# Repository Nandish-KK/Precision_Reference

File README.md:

#  2.5V Precision Reference

A compact 2.5V precision voltage reference module, ideal for use as a standalone reference when building analog circuit prototypes or for verifying the accuracy of your multimeter’s voltage range over time.

## Prototyping and Testing
The design required a low voltage source to make the Reference module as compact as possible. A CR2032 coin cell at 3V is the ideal candidate.
This requirement turns into a design constraint as the minimum operating voltage stated in the datasheet for the REF03 is 4.5V. The REF03 is a Low-Dropout
type Reference and is the best option to design a voltage reference due to its extremly low Temperature coefficient (10-50 ppm/C) and requires minimum passive components to operate.

### Charge pump
In order to generate a voltage that is sufficient to drive the REF03 above the minimum operating voltage a charge pump topology is implemented.
The charge pump consists of a variable frequency oscillator and a voltage doubler circuit. The oscillator is constructed using an SN74 logic inverter with
hysteresis and an RC feedback network. At 3V input, the circuit can generate a maximum of 5.6V but drops drastically depending on the load.
The quiescent current of the REF03 is around 1 mA, which also gives a bit of headroom to even sink some current into the DUT. 

Oscillator: SN74LVC2G14DBV sot23-6 soldered with passives on a proto pcb.

### Testing

The following tests are performed with a wide bandwidth. You can see some high-frequency noise along with voltage ripples at the charge pump output (with REF03 connected). After further testing, it seems like the ripples are generated from the oscillator.
The SN74LVC2G14DBV has a fast rising edge of about 4ns; this, combined with Schmitt trigger action and the board's parasitics, results in a ringing behavior at the output. This high-frequency component seems to bypass even the REF03 and appears at the reference voltage. Implementation of an additional filtering circuit might be necessary. Another option is to find an inverter with a slower rise time.

Tested the reference output with coax to make sure the noise isn't from a background source. The other two channels are connected to the charge pump output and the oscillator output.

- Yellow : Reference Output
- Pink :   Charge pump Output
- Blue :   Oscillator  Output

#### No Load condition

The voltmeter isn't accurate and is used to observe voltage drops with and without load.

With a high-impedance load like a multimeter (essentially no load) attached to the output of the REF03, the voltage is quite stable and exhibits minimal ripple.
The output voltage is around 5.47V with a ripple of 36.25mV peak-to-peak (7.54mV RMS). The setup also draws around 6mA, which is quite high. Since the REF03 draws 1-2 mA, the additional current should be consumed by the oscillator. This is not a good circuit to leave ON for a long time; it will drain the CR2032 in a day or two. Make sure to turn off the module with the toggle switch after use to prevent it from going completely dead. 

#### 10mA Load 
The charge pump output voltage seems to drop significantly if the REF03 starts to sink current to the load. The REF03 is rated to sink up to 24mA, but this much current will render my simple charge pump setup useless. I did end up testing the current sink capability of the prototype using a variable potentiometer, and it seems like the voltage starts to drop around 16mA of total current draw. This indicates that the prototype PCB was able to sink 10mA from the REF03 (remember that the circuit draws 6mA at idle). The voltage dropping trend was observed using a 3.5-digit multimeter, and results may vary with more accurate meters.

While sinking 16mA of total current, the charge pump output drops to around 4.87 volts while also exhibiting some ripple characteristics. The ripple is around 300mV peak-to-peak with a frequency that corresponds to the charge pump switching frequency. Thankfully, the ripple doesn't reflect on the output of the REF03. Note that these ripples can be minimized with appropriate capacitance.

## Output Stability

Currently, I don't own a precision multimeter, which makes it harder to measure how stable the output voltage really is. What I do own is a DSO with a 12-bit ADC (SDS800X), and it seems to read the voltage accurately up to 4 digits easily. The high-frequency noise at the output seems a bit annoying and likely skews the results a bit.

Reference voltage with No filter(Coupling: DC , BW: 20MHz)

## Filtering
In the end, I attempted to filter out the high-frequency noise using a simple RC filter with a cutoff frequency of around 1.5 kHz to achieve a more stable result. I also substituted the resistor with a ferrite bead. Both methods worked well in attenuating the noise. Although the filter did not eliminate it entirely, the noise was attenuated by approximately 20 dB when using the ferrite bead.

Noise measurement with a Ferrite Bead Pi Filter (Coupling: AC , BW: 20MHz)

Reference voltage with Ferrite Bead and a 10uF capacitor filter(Coupling: DC , BW: 20MHz)

## PCB Layout
The following schematic and PCB are designed with KiCad 9.

## Renders
- Tools:
  - pcb2blender addon for KiCad
  - Blender

---
## Dimensions

- PCB Diameter: 45mm
- Binding Post Spacing: 19.05mm 
- Mounting Holes: 2.2mm

## PCB Features

- Single coin cell operation (CR2032).
- Trim pot for fine adjustment of output voltage.
- 4mm BNC terminal with 3/4" spacing.
- Adjustment range: 2.3V - 2.8V.
- Compact design with M2 mounting holes and toggle switch.

---

## Datasheet

Datasheet: [Precision 2.5V, 5.0V, and 10.0V Voltage References](https://www.analog.com/media/en/technical-documentation/data-sheets/ref01_02_03.pdf)

```plaintext

## Some Design Afterthought's

- The REF03 datasheet specifies a minimum operating voltage of 4.5 V.
- However, during testing, the output remained stable down to 3 V with no load.
- If your application sinks significant current, ensure the supply voltage remains well above the minimum — ideally with a low-voltage cutoff circuit.
- The current consumption is quite high for operating from a single cell. Needs further investigation of the charge pump circuit.
- Also, the toggle switch seems to be upside down... D'oh!

```

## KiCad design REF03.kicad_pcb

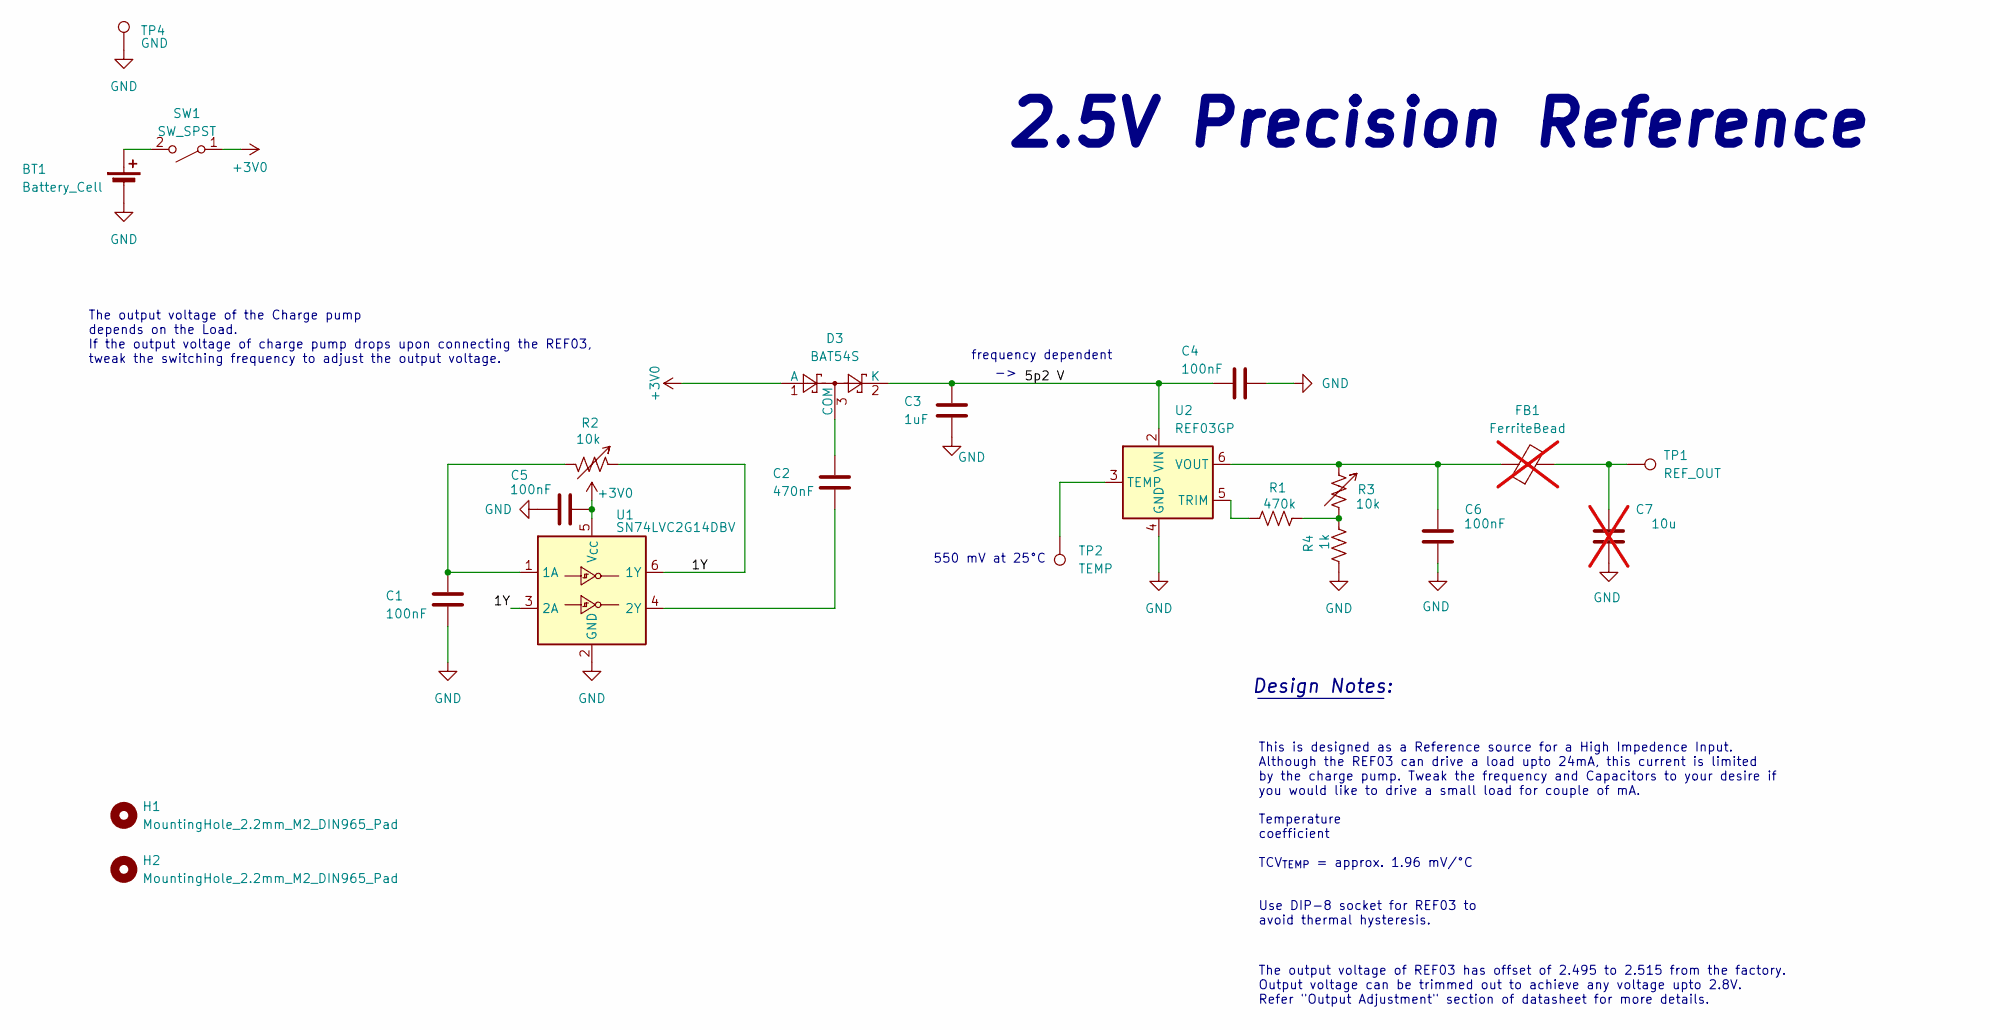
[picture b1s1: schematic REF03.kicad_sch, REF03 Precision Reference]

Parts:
BT1: Battery_Cell; BatteryHolder_Multicomp_BC-2001_1x2032
C1, C4, C5, C6: 100nF; C_0805_2012Metric
C2: 470nF; C_0805_2012Metric
C3: 1uF; C_1206_3216Metric
C7: 10u; C_0805_2012Metric; not fitted
D3: BAT54S; SOT-23
FB1: FerriteBead; L_0805_2012Metric; not fitted
H1, H2: MountingHole_2.2mm_M2_DIN965_Pad
R1: 470k; R_1206_3216Metric
R2, R3: 10k; Potentiometer_Bourns_3214G_Horizontal
R4: 1k; R_1206_3216Metric
SW1: SW_SPST; SW_Slide-03_Wuerth-WS-SLTV_10x2.5x6.4_P2.54mm
TP1: REF_OUT; TestPoint_Loop_D2.50mm_Drill1.0mm
TP2: TEMP; TestPoint_Pad_2.5x2.5mm
TP4: GND; TestPoint_Loop_D2.50mm_Drill1.0mm
U1: SN74LVC2G14DBV; SOT-23-6
U2: REF03GP; PowerIntegrations_SMD-8

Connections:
+3V0: C5.2, D3.1 (A), SW1.1 (A), U1.5 (V_{CC})
/1Y: R2.1, U1.3 (2A), U1.6 (1Y)
/5p2 V: C3.1, C4.2, D3.2 (K), U2.2 (VIN)
GND: BT1.2 (-), C1.2, C3.2, C4.1, C5.1, C6.1, C7.1, R4.1, TP4.1, U1.2 (GND), U2.4 (GND)
unnamed: BT1.1 (+), SW1.2 (B)
unnamed: C7.2, FB1.2, TP1.1
unnamed: C2.1, D3.3 (COM)
unnamed: R1.2, R3.2, R4.2
unnamed: C1.1, R2.2, U1.1 (1A)
unnamed: C2.2, U1.4 (2Y)
unnamed: TP2.1, U2.3 (TEMP)
unnamed: R1.1, U2.5 (TRIM)
unnamed: C6.2, FB1.1, R3.1, U2.6 (VOUT)

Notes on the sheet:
550 mV at 25°C
The output voltage of the Charge pump depends on the Load. If the output voltage of charge pump drops upon connecting the REF03, tweak the switching frequency to adjust the output voltage.
Design Notes:
2.5V Precision Reference
Use DIP-8 socket for REF03 to avoid thermal hysteresis.
Temperature coefficient TCV_{TEMP} = approx. 1.96 mV/°C
The output voltage of REF03 has offset of 2.495 to 2.515 from the factory. Output voltage can be trimmed out to achieve any voltage upto 2.8V. Refer "Output Adjustment" section of datasheet for more details.
This is designed as a Reference source for a High Impedence Input. Although the REF03 can drive a load upto 24mA, this current is limited by the charge pump. Tweak the frequency and Capacitors to your desire if you would like to drive a small load for couple of mA.
frequency dependent

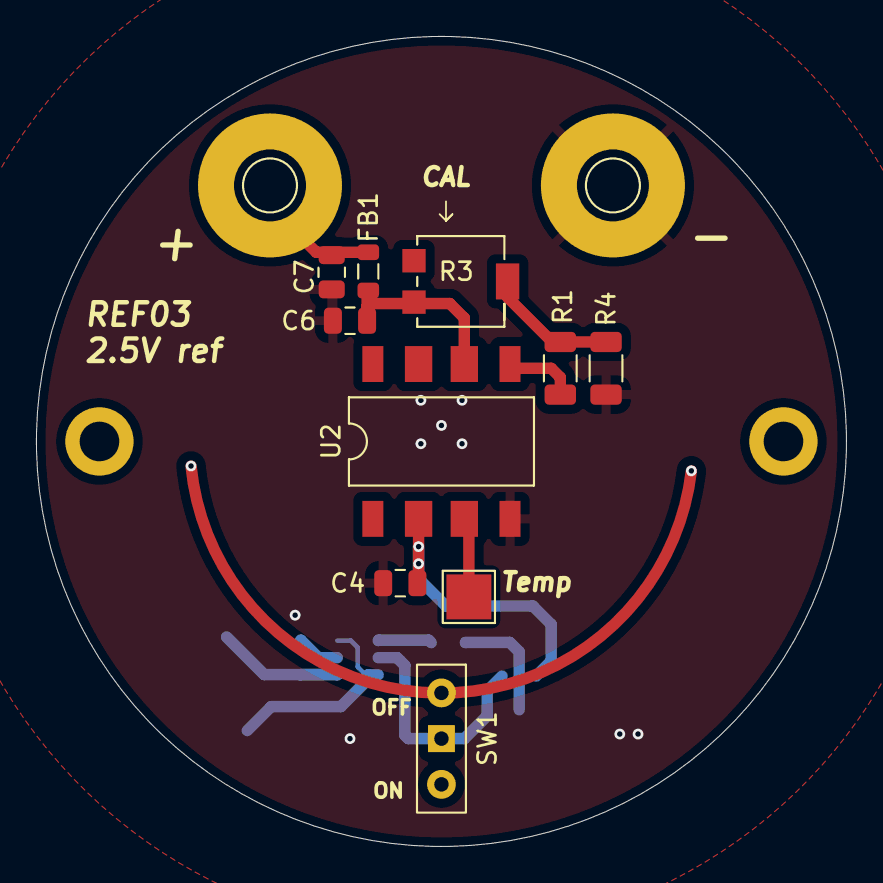
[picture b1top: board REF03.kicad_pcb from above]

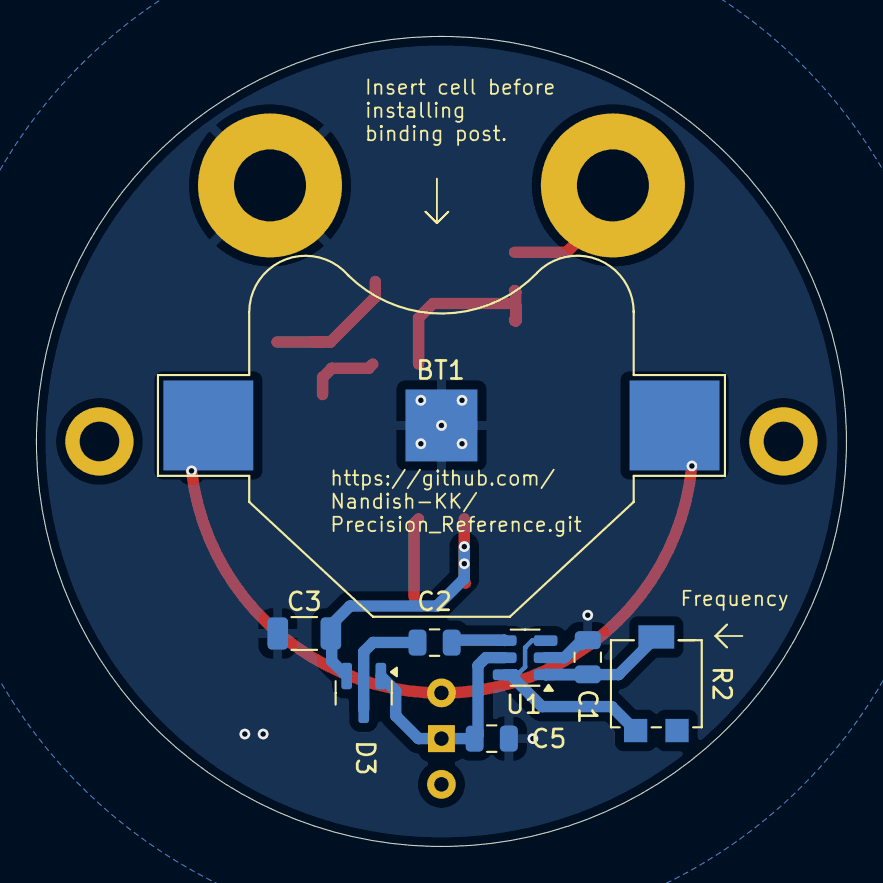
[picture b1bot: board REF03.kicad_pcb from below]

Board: 2 copper layers, 45.0 x 45.0 mm, 22 parts (8 on the bottom side), 13 nets.

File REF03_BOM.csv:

"Reference","Qty","Value","DNP","Exclude from BOM","Exclude from Board","Footprint","Datasheet"
"BT1","1","Battery_Cell","","","","Battery:BatteryHolder_Multicomp_BC-2001_1x2032","~"
"C1,C4,C5,C6","4","100nF","","","","Capacitor_SMD:C_0805_2012Metric","~"
"C2","1","470nF","","","","Capacitor_SMD:C_0805_2012Metric","~"
"C3","1","1uF","","","","Capacitor_SMD:C_1206_3216Metric","~"
"D3","1","BAT54S","","","","Package_TO_SOT_SMD:SOT-23","https://www.diodes.com/assets/Datasheets/ds11005.pdf"
"R1","1","470k","","","","Resistor_SMD:R_1206_3216Metric","~"
"R2,R3","2","10k","","","","Potentiometer_SMD:Potentiometer_Bourns_3214G_Horizontal","~"
"R4","1","1k","","","","Resistor_SMD:R_1206_3216Metric","~"
"SW1","1","SW_SPST","","","","Button_Switch_THT:SW_Slide-03_Wuerth-WS-SLTV_10x2.5x6.4_P2.54mm","~"
"TP1","1","REF_OUT","","","","TestPoint:TestPoint_Loop_D2.50mm_Drill1.0mm","~"
"TP2","1","TEMP","","","","TestPoint:TestPoint_Pad_2.5x2.5mm","~"
"TP4","1","GND","","","","TestPoint:TestPoint_Loop_D2.50mm_Drill1.0mm","~"
"U1","1","SN74LVC2G14DBV","","","","Package_TO_SOT_SMD:SOT-23-6","https://www.ti.com/lit/ds/symlink/sn74lvc2g14.pdf"
"U2","1","REF03GP","","","","Package_DIP:PowerIntegrations_SMD-8","https://www.analog.com/media/en/technical-documentation/data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"

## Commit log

2025-07-12 Added BOM, Dimensions
2025-07-12 added README.md, Render
2025-07-13 Added REF03_Dimensions,updated Readme
2025-07-14 Updated readme and added photos of the prototype
2026-01-20 Rename Prototype_REF03_module.jpg to Render.jpg
2026-01-20 Fix formatting and improve clarity in README
